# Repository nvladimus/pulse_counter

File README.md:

# pulse_counter
 Arduino code for counting trigger pulses from external device (camera, stage, etc)

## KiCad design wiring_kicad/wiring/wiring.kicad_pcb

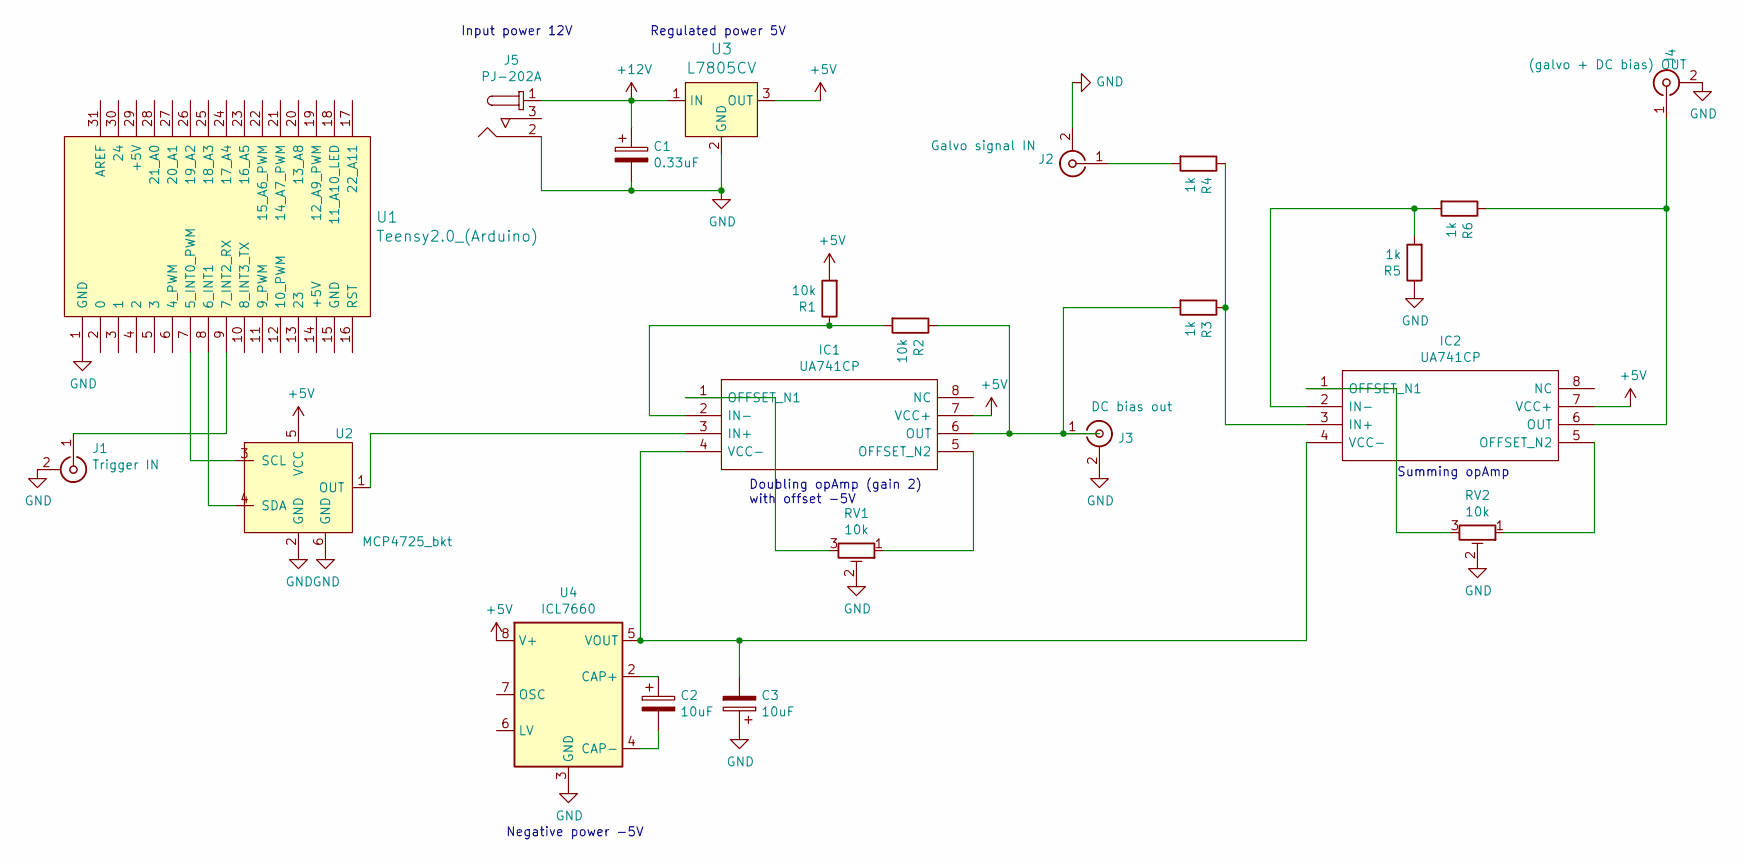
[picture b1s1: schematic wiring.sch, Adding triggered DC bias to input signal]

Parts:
C1: 0.33uF; CP_Radial_Tantal_D4.5mm_P2.50mm
C2, C3: 10uF; CP_Radial_D4.0mm_P1.50mm
IC1, IC2: UA741CP; DIP-8_W7.62mm; Mouser Part Number 595-UA741CP
J1: Trigger IN; BNC_female_jack_TE_1-1634505-0
J2: Galvo signal IN; BNC_female_jack_TE_1-1634505-0
J3: DC bias out; BNC_female_jack_TE_1-1634505-0
J4: (galvo + DC bias) OUT; BNC_female_jack_TE_1-1634505-0
J5: PJ-202A; Barrel_Jack_5.5mmODx2.1mmID_PJ-202A; MPN PJ-202A; Digi-Key_PN CP-202A-ND
R1, R2: 10k; R_Axial_DIN0207_L6.3mm_D2.5mm_P10.16mm_Horizontal
R3, R4, R5, R6: 1k; R_Axial_DIN0207_L6.3mm_D2.5mm_P10.16mm_Horizontal
RV1, RV2: 10k; PinHeader_1x3_P2.5mm_Drill1.1mm
U1: Teensy2.0_(Arduino); Teensy2.0
U2: MCP4725_bkt; MCP4725
U3: L7805CV; TO-220-3; MPN L7805CV; Digi-Key_PN 497-1443-5-ND
U4: ICL7660; DIP-8_W7.62mm

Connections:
+5V: IC1.7 (VCC+), IC2.7 (VCC+), R1.2, U2.5 (VCC), U3.3 (OUT), U4.8 (V+)
+12V: C1.1, J5.1, U3.1 (IN)
GND: C1.2, C3.1, J1.2 (Ext), J2.2 (Ext), J3.2 (Ext), J4.2 (Ext), J5.2, R5.1, RV1.2, RV2.2, U1.1 (GND), U2.2 (GND), U2.6 (GND), U3.2 (GND), U4.3 (GND)
unnamed: C2.1, U4.2 (CAP+)
unnamed: C2.2, U4.4 (CAP-)
unnamed: C3.2, IC1.4 (VCC-), IC2.4 (VCC-), U4.5 (VOUT)
unnamed: IC1.1 (OFFSET_N1), RV1.3
unnamed: IC1.2 (IN-), R1.1, R2.2
unnamed: IC1.3 (IN+), U2.1 (OUT)
unnamed: IC1.5 (OFFSET_N2), RV1.1
unnamed: IC1.6 (OUT), J3.1 (In), R2.1, R3.2
unnamed: IC2.1 (OFFSET_N1), RV2.3
unnamed: IC2.2 (IN-), R5.2, R6.2
unnamed: IC2.3 (IN+), R3.1, R4.1
unnamed: IC2.5 (OFFSET_N2), RV2.1
unnamed: IC2.6 (OUT), J4.1 (In), R6.1
unnamed: J1.1 (In), U1.9 (7_INT2_RX)
unnamed: J2.1 (In), R4.2
unnamed: U1.7 (5_INT0_PWM), U2.3 (SCL)
unnamed: U1.8 (6_INT1), U2.4 (SDA)

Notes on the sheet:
Regulated power 5V
Negative power -5V
Doubling opAmp (gain 2) with offset -5V
Summing opAmp
Input power 12V

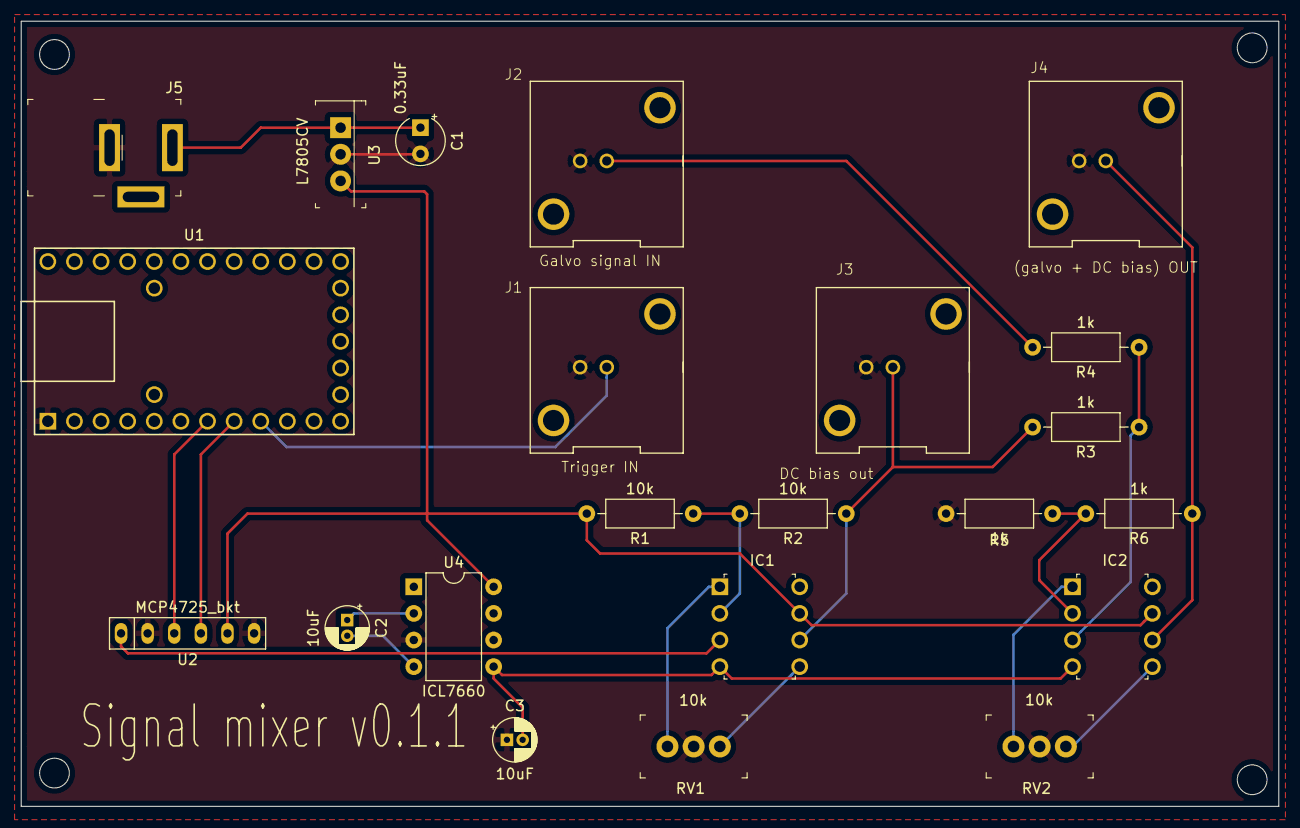
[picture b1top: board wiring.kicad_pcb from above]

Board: 2 copper layers, 120.0 x 74.9 mm, 22 parts (0 on the bottom side), 20 nets.

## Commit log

2019-09-14 first commit
    Blink LED on every rising edge of digital input at pin 5.
2019-09-16 changed input pin
2019-09-16 comments
2019-09-16 wired to MCP4725 DAC chip, switching works
2019-09-17 cleaned up, added Fritzing wiring diagram
    Diagram uses Adafruit breakout board and Teensy 2.0.
2019-09-17 added bi-polar AO generator wiring
2019-09-21 made PCB in KiCAD
2019-10-02 fixed PCB bug, added serial comm to Teensy board
2019-10-07 fixed reset bug
2019-10-08 fixed bugs
2019-11-01 added version query command
2019-11-04 Update LICENSE
